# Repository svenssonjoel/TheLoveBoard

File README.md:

# TheLoveBoard
Kicad microcontroller pcb

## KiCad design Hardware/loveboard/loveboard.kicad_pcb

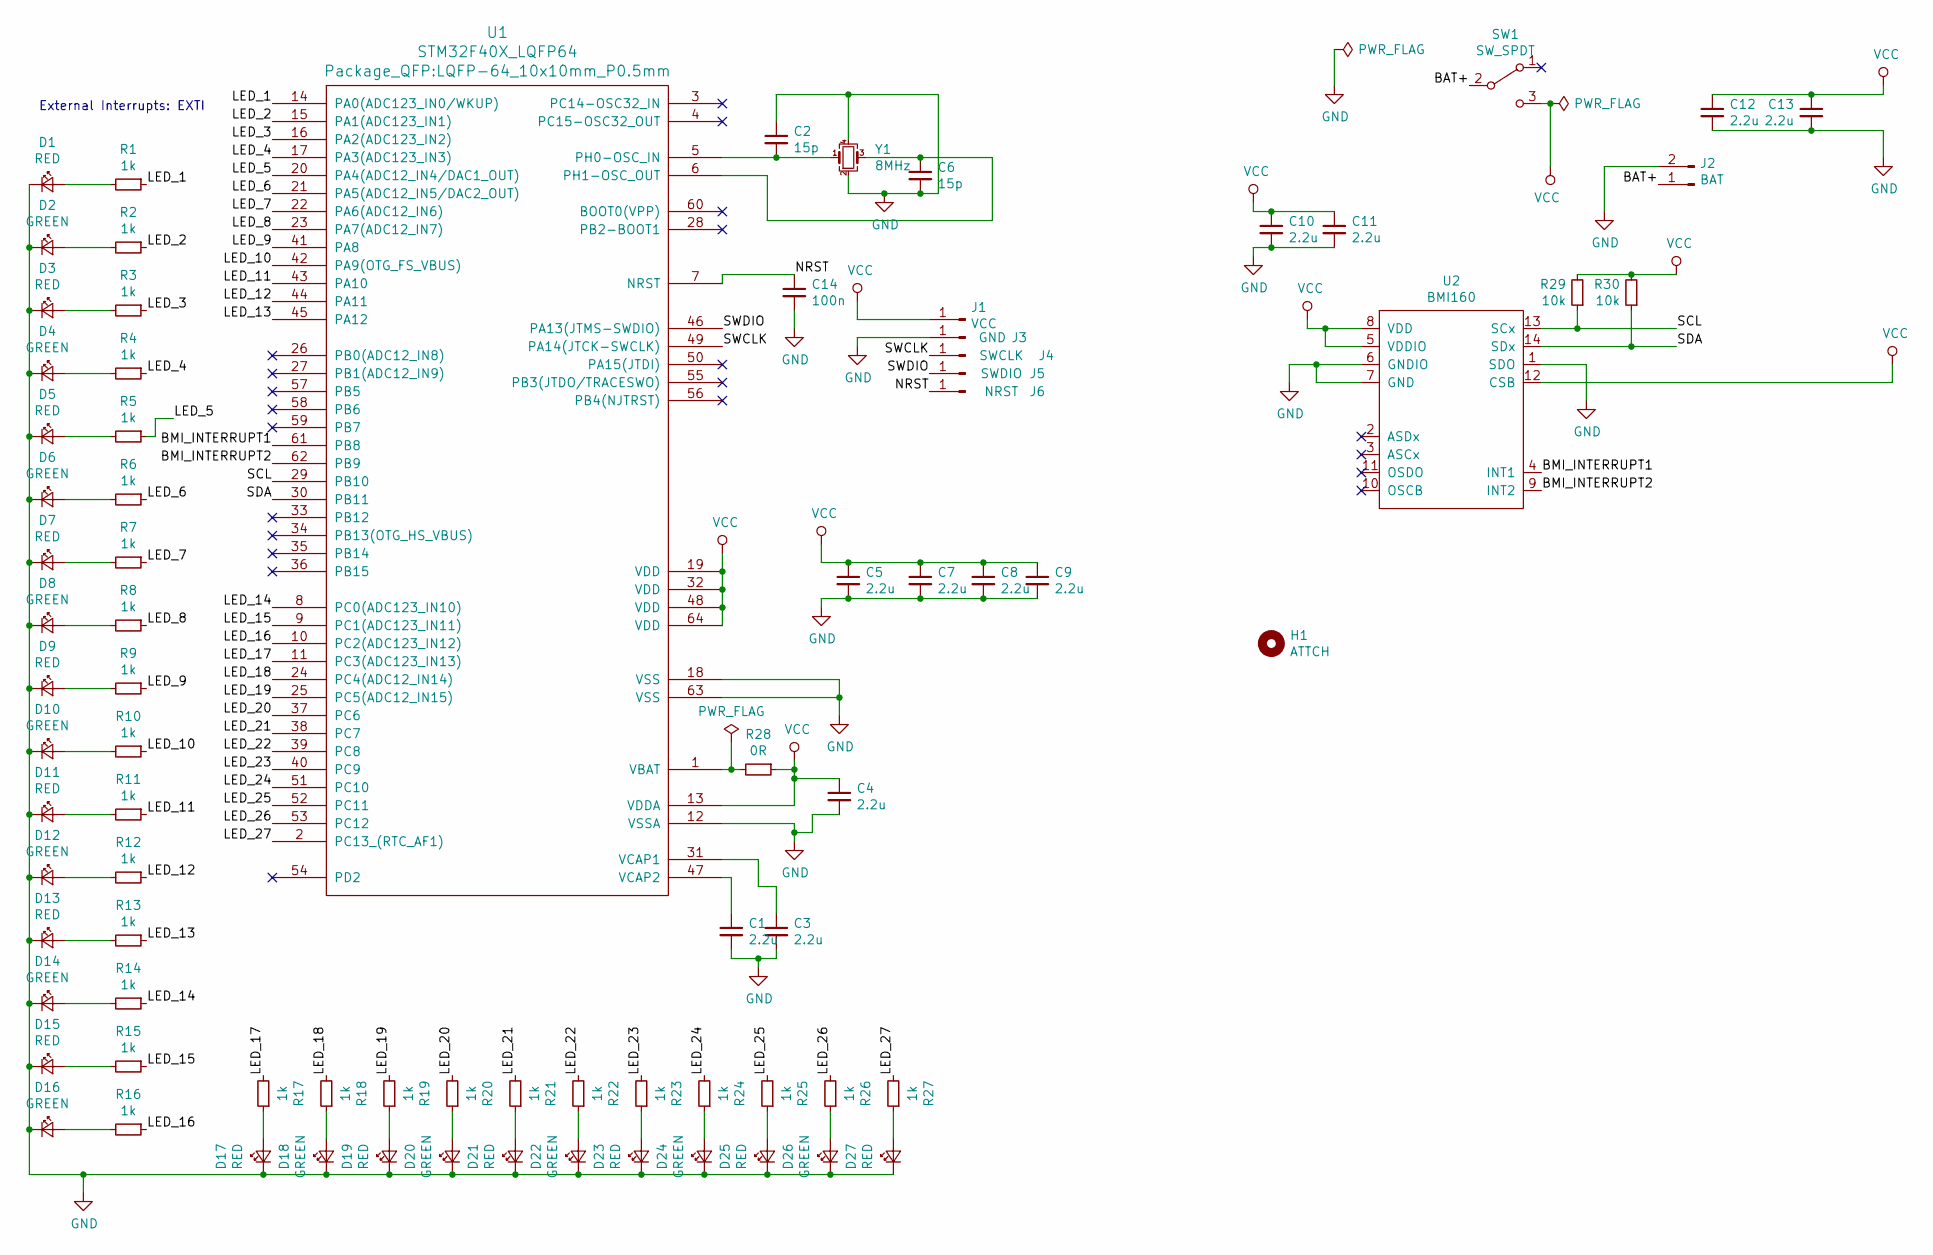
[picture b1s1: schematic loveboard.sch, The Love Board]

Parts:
C1, C3, C4, C5, C7, C8, C9, C10, C11, C12, C13: 2.2u; C_0603_1608Metric
C2, C6: 15p; C_0603_1608Metric
C14: 100n; C_0603_1608Metric
D1, D3, D5, D7, D9, D11, D13, D15, D17, D19, D21, D23, D25, D27: RED; LED_0603_1608Metric
D2, D4, D6, D8, D10, D12, D14, D16, D18, D20, D22, D24, D26: GREEN; LED_0603_1608Metric
H1: ATTCH; MountingHole_2.5mm
J1: VCC; TestPoint_Pad_D3.0mm
J2: BAT; BatteryHolder_Keystone_1060_1x2032
J3: GND; TestPoint_Pad_D3.0mm
J4: SWCLK; TestPoint_Pad_D3.0mm
J5: SWDIO; TestPoint_Pad_D3.0mm
J6: NRST; TestPoint_Pad_D3.0mm
R1, R2, R3, R4, R5, R6, R7, R8, R9, R10, R11, R12, R13, R14, R15, R16, R17, R18, R19, R20, R21, R22, R23, R24, R25, R26, R27: 1k; R_0603_1608Metric
R28: 0R; R_0603_1608Metric
R29, R30: 10k; R_0603_1608Metric
SW1: SW_SPDT; SW_SPDT_PCM12
U1: STM32F40X_LQFP64; LQFP-64_10x10mm_P0.5mm
U2: BMI160; Bosch_LGA-14_3x2.5mm_P0.5mm
Y1: 8MHz; Crystal_SMD_5032-4Pin_5.0x3.2mm

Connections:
/BAT+: J2.1, SW1.2 (B)
/BMI_INTERRUPT1: U1.61 (PB8), U2.4 (INT1)
/BMI_INTERRUPT2: U1.62 (PB9), U2.9 (INT2)
/LED_1: R1.1, U1.14 (PA0(ADC123_IN0/WKUP))
/LED_2: R2.1, U1.15 (PA1(ADC123_IN1))
/LED_3: R3.1, U1.16 (PA2(ADC123_IN2))
/LED_4: R4.1, U1.17 (PA3(ADC123_IN3))
/LED_5: R5.1, U1.20 (PA4(ADC12_IN4/DAC1_OUT))
/LED_6: R6.1, U1.21 (PA5(ADC12_IN5/DAC2_OUT))
/LED_7: R7.1, U1.22 (PA6(ADC12_IN6))
/LED_8: R8.1, U1.23 (PA7(ADC12_IN7))
/LED_9: R9.1, U1.41 (PA8)
/LED_10: R10.1, U1.42 (PA9(OTG_FS_VBUS))
/LED_11: R11.1, U1.43 (PA10)
/LED_12: R12.1, U1.44 (PA11)
/LED_13: R13.1, U1.45 (PA12)
/LED_14: R14.1, U1.8 (PC0(ADC123_IN10))
/LED_15: R15.1, U1.9 (PC1(ADC123_IN11))
/LED_16: R16.1, U1.10 (PC2(ADC123_IN12))
/LED_17: R17.2, U1.11 (PC3(ADC123_IN13))
/LED_18: R18.2, U1.24 (PC4(ADC12_IN14))
/LED_19: R19.2, U1.25 (PC5(ADC12_IN15))
/LED_20: R20.2, U1.37 (PC6)
/LED_21: R21.2, U1.38 (PC7)
/LED_22: R22.2, U1.39 (PC8)
/LED_23: R23.2, U1.40 (PC9)
/LED_24: R24.2, U1.51 (PC10)
/LED_25: R25.2, U1.52 (PC11)
/LED_26: R26.2, U1.53 (PC12)
/LED_27: R27.2, U1.2 (PC13_(RTC_AF1))
/NRST: C14.1, J6.1, U1.7 (NRST)
/SCL: R29.1, U1.29 (PB10), U2.13 (SCx)
/SDA: R30.1, U1.30 (PB11), U2.14 (SDx)
/SWCLK: J4.1, U1.49 (PA14(JTCK-SWCLK))
/SWDIO: J5.1, U1.46 (PA13(JTMS-SWDIO))
GND: C1.2, C2.1, C3.2, C4.2, C5.2, C6.2, C7.2, C8.2, C9.2, C10.2, C11.2, C12.2, C13.2, C14.2, D1.1 (K), D2.1 (K), D3.1 (K), D4.1 (K), D5.1 (K), D6.1 (K), D7.1 (K), D8.1 (K), D9.1 (K), D10.1 (K), D11.1 (K), D12.1 (K), D13.1 (K), D14.1 (K), D15.1 (K), D16.1 (K), D17.1 (K), D18.1 (K), D19.1 (K), D20.1 (K), D21.1 (K), D22.1 (K), D23.1 (K), D24.1 (K), D25.1 (K), D26.1 (K), D27.1 (K), J2.2, J3.1, U1.12 (VSSA), U1.18 (VSS), U1.63 (VSS), U2.1 (SDO), U2.6 (GNDIO), U2.7 (GND), Y1.2, Y1.4
unnamed: C1.1, U1.47 (VCAP2)
unnamed: C2.2, U1.5 (PH0-OSC_IN), Y1.1
unnamed: C3.1, U1.31 (VCAP1)
unnamed: C6.1, U1.6 (PH1-OSC_OUT), Y1.3
unnamed: D1.2 (A), R1.2
unnamed: D2.2 (A), R2.2
unnamed: D3.2 (A), R3.2
unnamed: D4.2 (A), R4.2
unnamed: D5.2 (A), R5.2
unnamed: D6.2 (A), R6.2
unnamed: D7.2 (A), R7.2
unnamed: D8.2 (A), R8.2
unnamed: D9.2 (A), R9.2
unnamed: D10.2 (A), R10.2
unnamed: D11.2 (A), R11.2
unnamed: D12.2 (A), R12.2
unnamed: D13.2 (A), R13.2
unnamed: D14.2 (A), R14.2
unnamed: D15.2 (A), R15.2
unnamed: D16.2 (A), R16.2
unnamed: D17.2 (A), R17.1
unnamed: D18.2 (A), R18.1
unnamed: D19.2 (A), R19.1
unnamed: D20.2 (A), R20.1
unnamed: D21.2 (A), R21.1
unnamed: D22.2 (A), R22.1
unnamed: D23.2 (A), R23.1
unnamed: D24.2 (A), R24.1
unnamed: D25.2 (A), R25.1
unnamed: D26.2 (A), R26.1
unnamed: D27.2 (A), R27.1
unnamed: R28.2, U1.1 (VBAT)
VCC: C4.1, C5.1, C7.1, C8.1, C9.1, C10.1, C11.1, C12.1, C13.1, J1.1, R28.1, R29.2, R30.2, SW1.3 (C), U1.13 (VDDA), U1.19 (VDD), U1.32 (VDD), U1.48 (VDD), U1.64 (VDD), U2.5 (VDDIO), U2.8 (VDD), U2.12 (CSB)

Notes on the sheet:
External Interrupts: EXTI

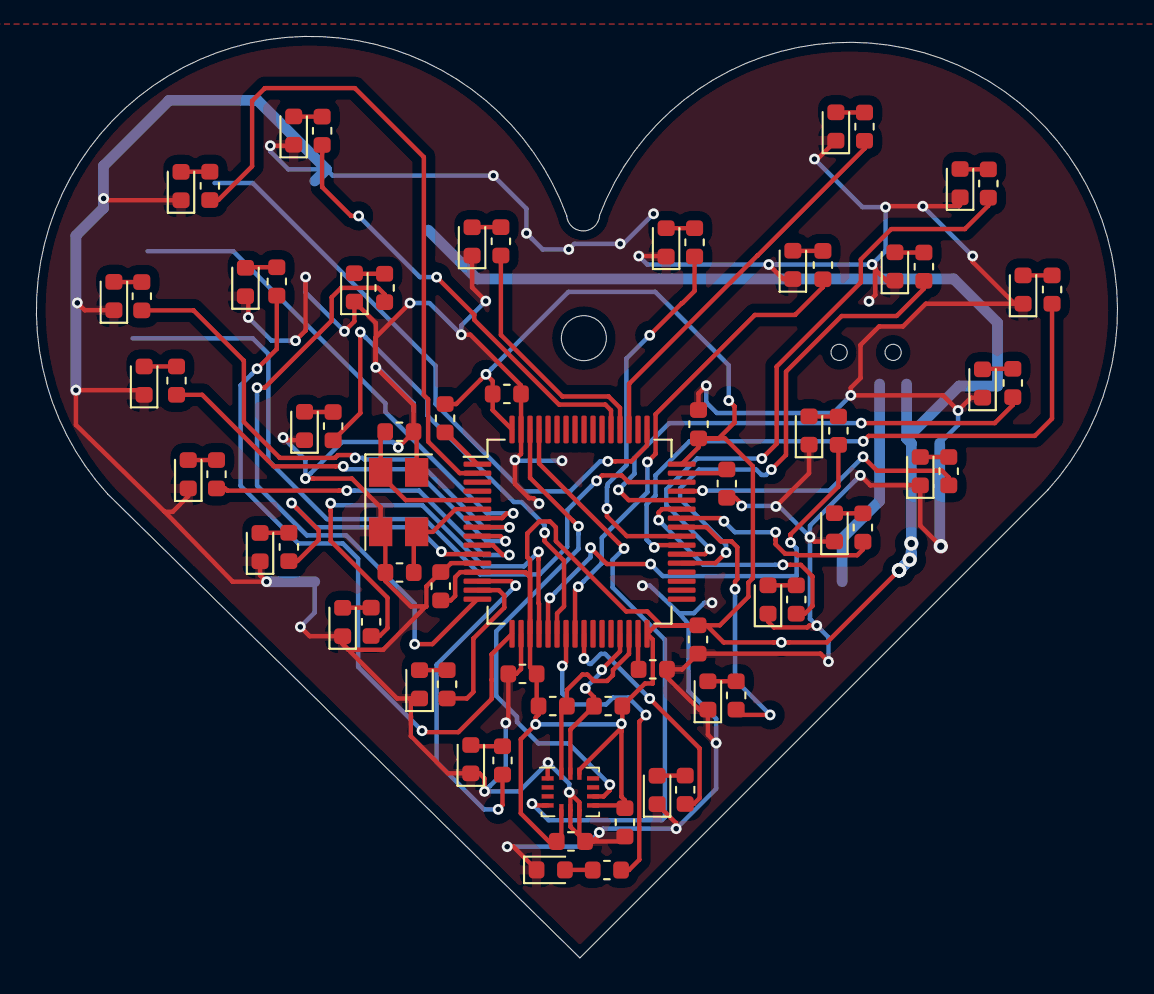
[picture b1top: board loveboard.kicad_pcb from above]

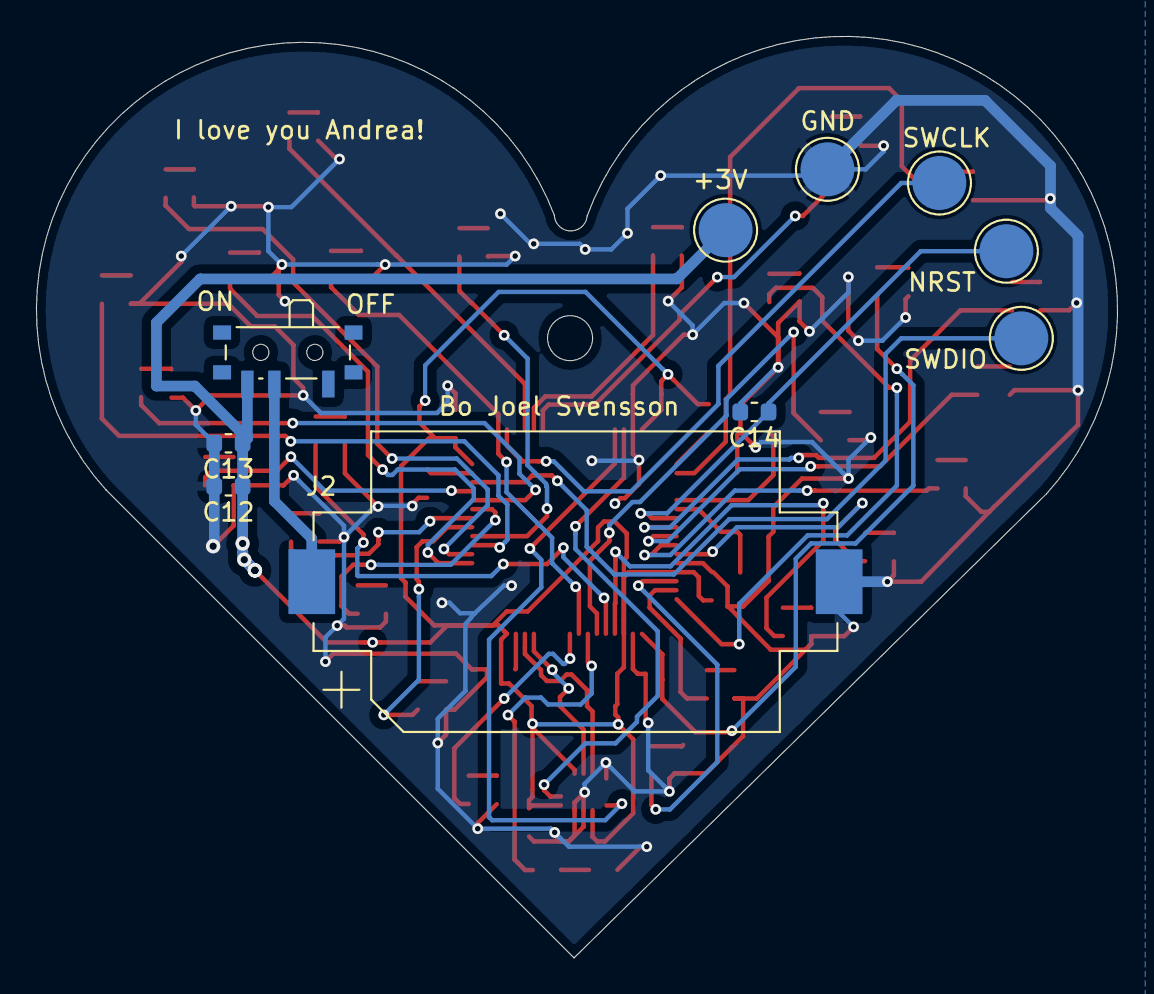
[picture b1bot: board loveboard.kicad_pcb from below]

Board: 2 copper layers, 60.1 x 51.2 mm, 82 parts (10 on the bottom side), 69 nets.

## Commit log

2019-12-07 pushing all the hard work up to github
2019-12-08 done
2019-12-08 added gerber
2019-12-08 order numbers
2020-01-08 added some initial firmware files
2020-01-11 added stm32 cfg for openocd
